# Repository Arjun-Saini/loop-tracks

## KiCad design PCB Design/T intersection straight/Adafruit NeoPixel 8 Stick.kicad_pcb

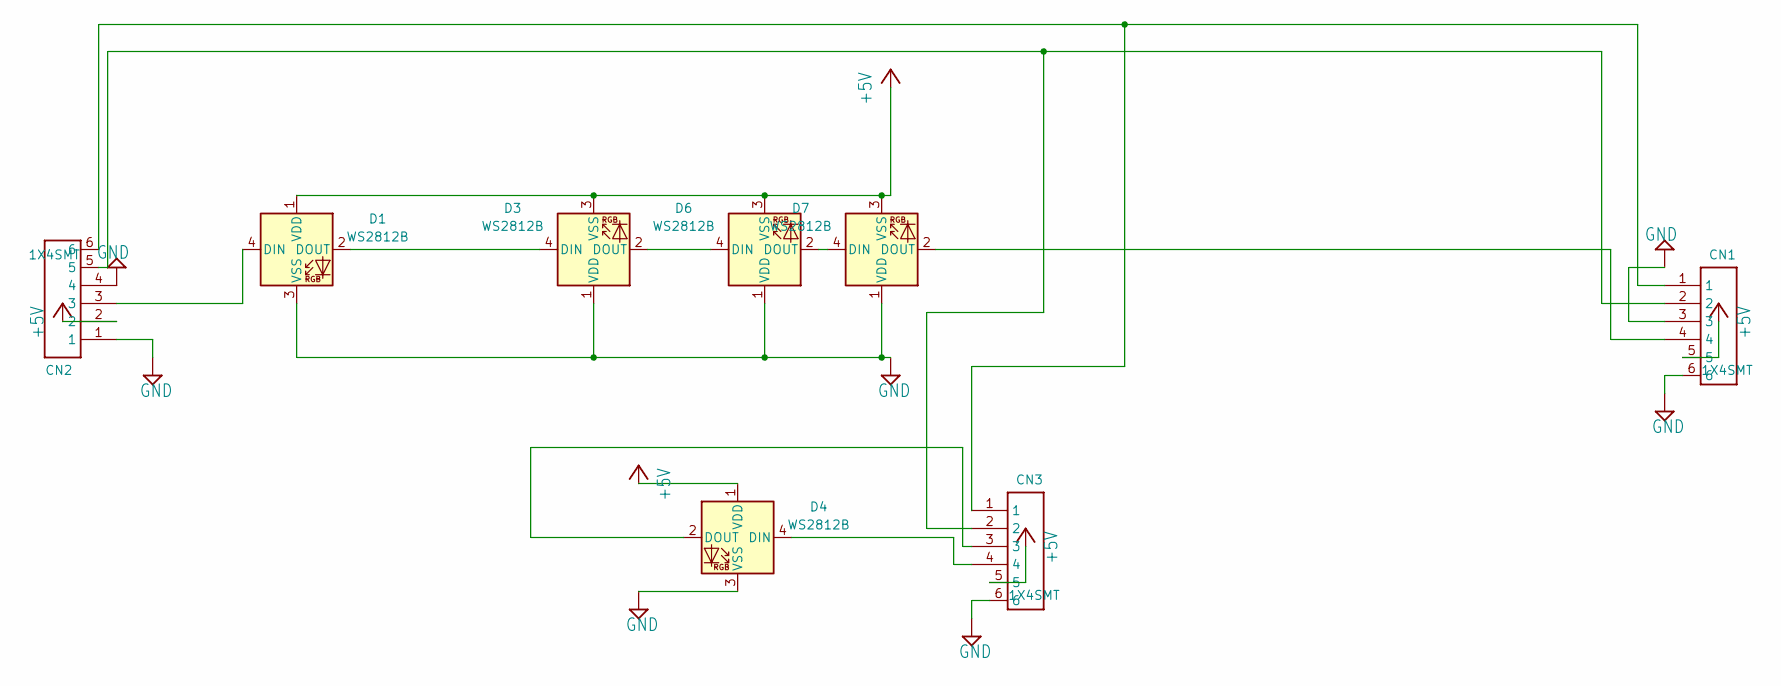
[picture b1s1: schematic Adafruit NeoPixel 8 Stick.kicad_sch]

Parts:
CN1, CN2, CN3: 1X4SMT; 1X4-SMT
D1, D3, D4, D6, D7: WS2812B; LED_WS2812B_PLCC4_5.0x5.0mm_P3.2mm

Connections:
+5V: CN1.5, CN2.2, CN3.5, D1.1 (VDD), D3.3 (VSS), D4.1 (VDD), D6.3 (VSS), D7.3 (VSS)
GND: CN1.3, CN1.6, CN2.1, CN2.4, CN3.6, D1.3 (VSS), D3.1 (VDD), D4.3 (VSS), D6.1 (VDD), D7.1 (VDD)
unnamed: CN1.1, CN2.6, CN3.1
unnamed: CN1.2, CN2.5, CN3.2
unnamed: CN1.4, D7.2 (DOUT)
unnamed: CN2.3, D1.4 (DIN)
unnamed: CN3.3, D4.2 (DOUT)
unnamed: CN3.4, D4.4 (DIN)
unnamed: D1.2 (DOUT), D3.4 (DIN)
unnamed: D3.2 (DOUT), D6.4 (DIN)
unnamed: D6.2 (DOUT), D7.4 (DIN)

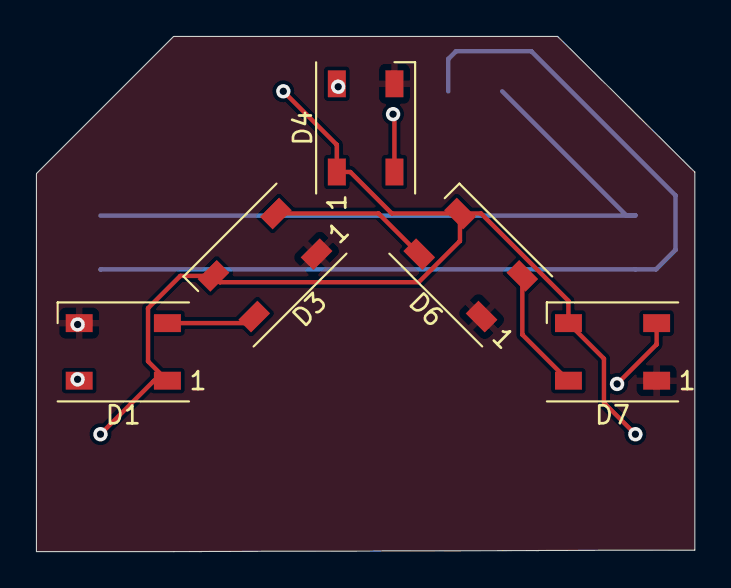
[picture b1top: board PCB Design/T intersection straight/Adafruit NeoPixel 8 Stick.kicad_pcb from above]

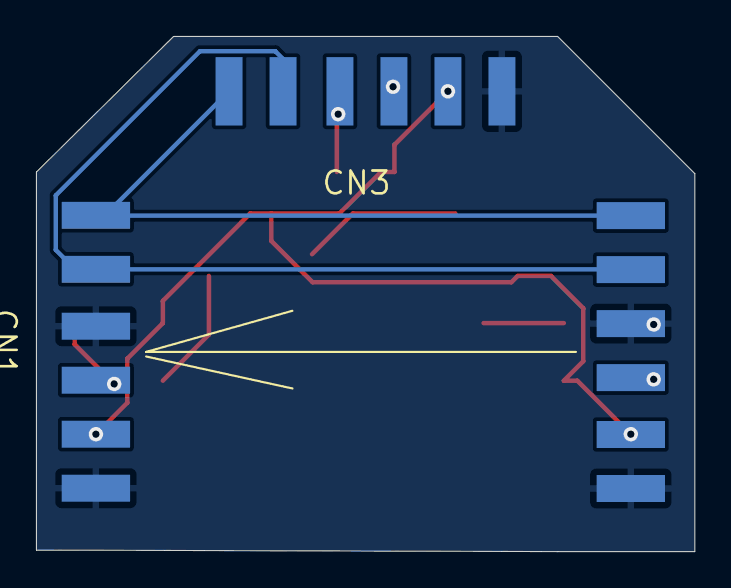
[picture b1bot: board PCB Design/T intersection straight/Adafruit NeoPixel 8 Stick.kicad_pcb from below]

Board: 2 copper layers, 36.6 x 28.6 mm, 8 parts (3 on the bottom side), 11 nets.

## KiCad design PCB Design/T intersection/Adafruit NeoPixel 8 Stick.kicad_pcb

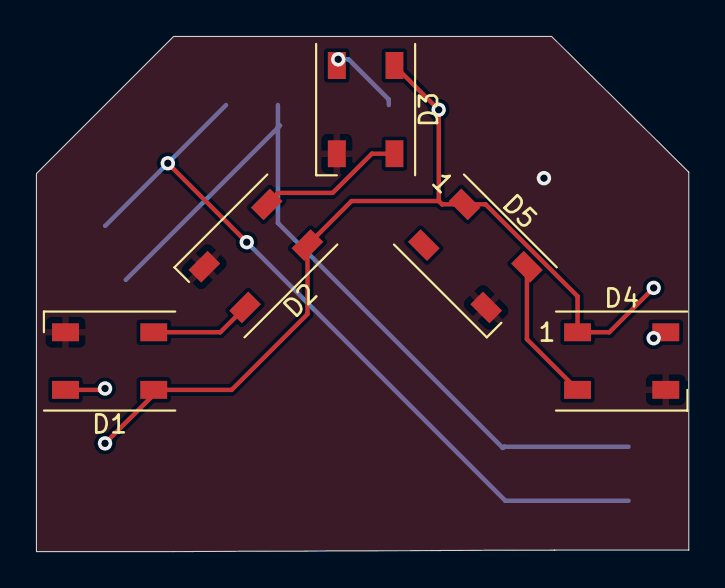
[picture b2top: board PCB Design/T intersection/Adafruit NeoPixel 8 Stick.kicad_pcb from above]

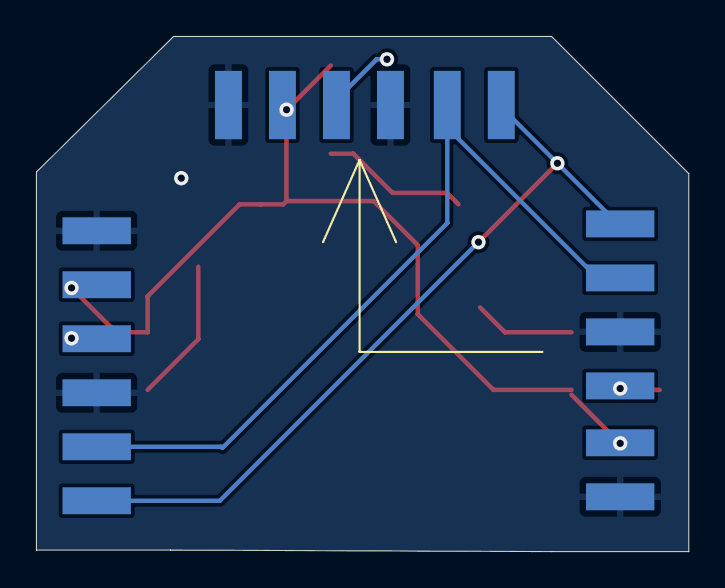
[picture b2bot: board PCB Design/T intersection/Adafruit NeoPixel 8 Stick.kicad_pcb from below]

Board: 2 copper layers, 36.2 x 28.6 mm, 8 parts (3 on the bottom side), 10 nets.

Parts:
CN1, CN2, CN3: 1X4SMT; 1X4-SMT
D1, D2, D3, D4, D5: WS2812B; LED_WS2812B_PLCC4_5.0x5.0mm_P3.2mm

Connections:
+5V: CN1.5, CN2.2, CN3.2, D1.1 (VDD), D2.1 (VDD), D3.1 (VDD), D4.1 (VDD), D5.1 (VDD)
GND: CN1.3, CN1.6, CN2.1, CN2.4, CN3.1, CN3.4, D1.3 (VSS), D2.3 (VSS), D3.3 (VSS), D4.3 (VSS), D5.3 (VSS)
unnamed: CN1.1, CN2.6, CN3.6
unnamed: CN1.2, CN2.5, CN3.5
unnamed: CN1.4, D3.2 (DOUT)
unnamed: CN2.3, D1.4 (DIN)
unnamed: CN3.3, D4.4 (DIN)
unnamed: D1.2 (DOUT), D2.4 (DIN)
unnamed: D2.2 (DOUT), D3.4 (DIN)
unnamed: D4.2 (DOUT), D5.4 (DIN)

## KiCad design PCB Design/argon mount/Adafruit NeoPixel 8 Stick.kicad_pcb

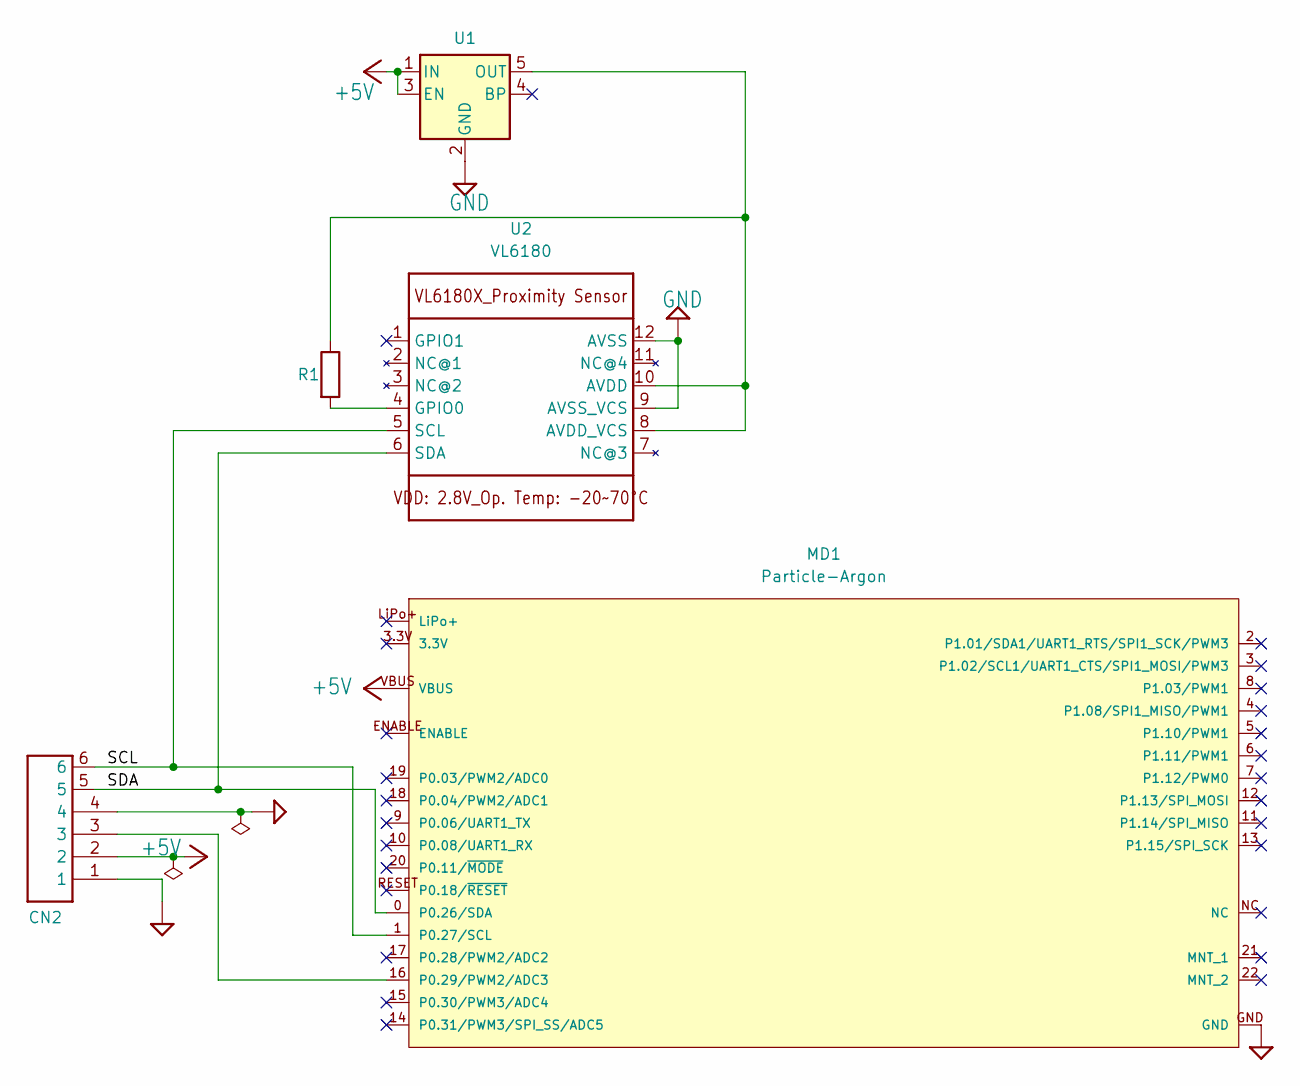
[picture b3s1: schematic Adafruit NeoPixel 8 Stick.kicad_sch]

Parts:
CN2: 1X4SMT; 1X4-SMT
MD1: Particle-Argon; Particle-Argon-0-0-MD1; manufacturer Particle; digikey description Bluetooth, WiFi 802.11b/g/n, Bluetooth 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
R1: R; R_Axial_DIN0207_L6.3mm_D2.5mm_P7.62mm_Horizontal
U1: MIC5219-2.85YM5; SOT-23-5
U2: VL6180

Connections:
+5V: CN2.2, MD1.VBUS, U1.1 (IN), U1.3 (EN)
/SCL: CN2.6, MD1.1 (P0.27/SCL), U2.5 (SCL)
/SDA: CN2.5, MD1.0 (P0.26/SDA), U2.6 (SDA)
GND: CN2.1, CN2.4, MD1.GND, U1.2 (GND), U2.9 (AVSS_VCS), U2.12 (AVSS)
unnamed: CN2.3, MD1.16 (P0.29/PWM2/ADC3)
unnamed: R1.1, U1.5 (OUT), U2.8 (AVDD_VCS), U2.10 (AVDD)
unnamed: R1.2, U2.4 (GPIO0)

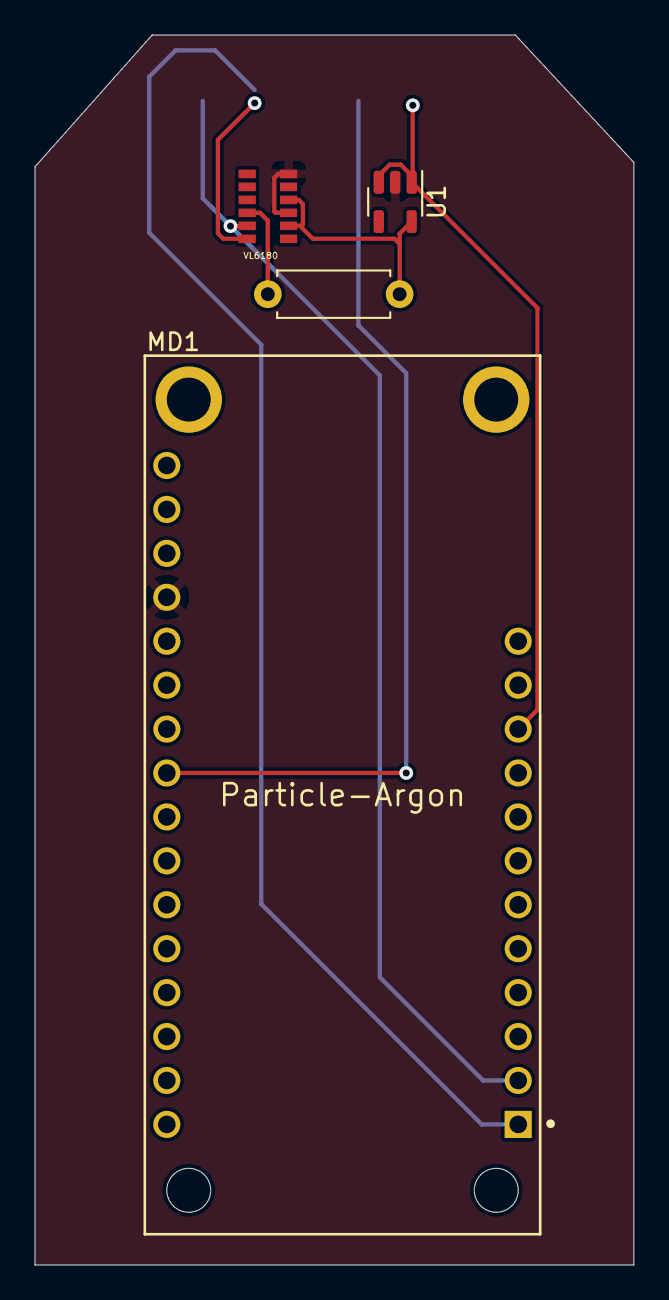
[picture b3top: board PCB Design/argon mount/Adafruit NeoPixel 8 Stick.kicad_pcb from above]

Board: 2 copper layers, 34.6 x 71.1 mm, 5 parts (1 on the bottom side), 7 nets.

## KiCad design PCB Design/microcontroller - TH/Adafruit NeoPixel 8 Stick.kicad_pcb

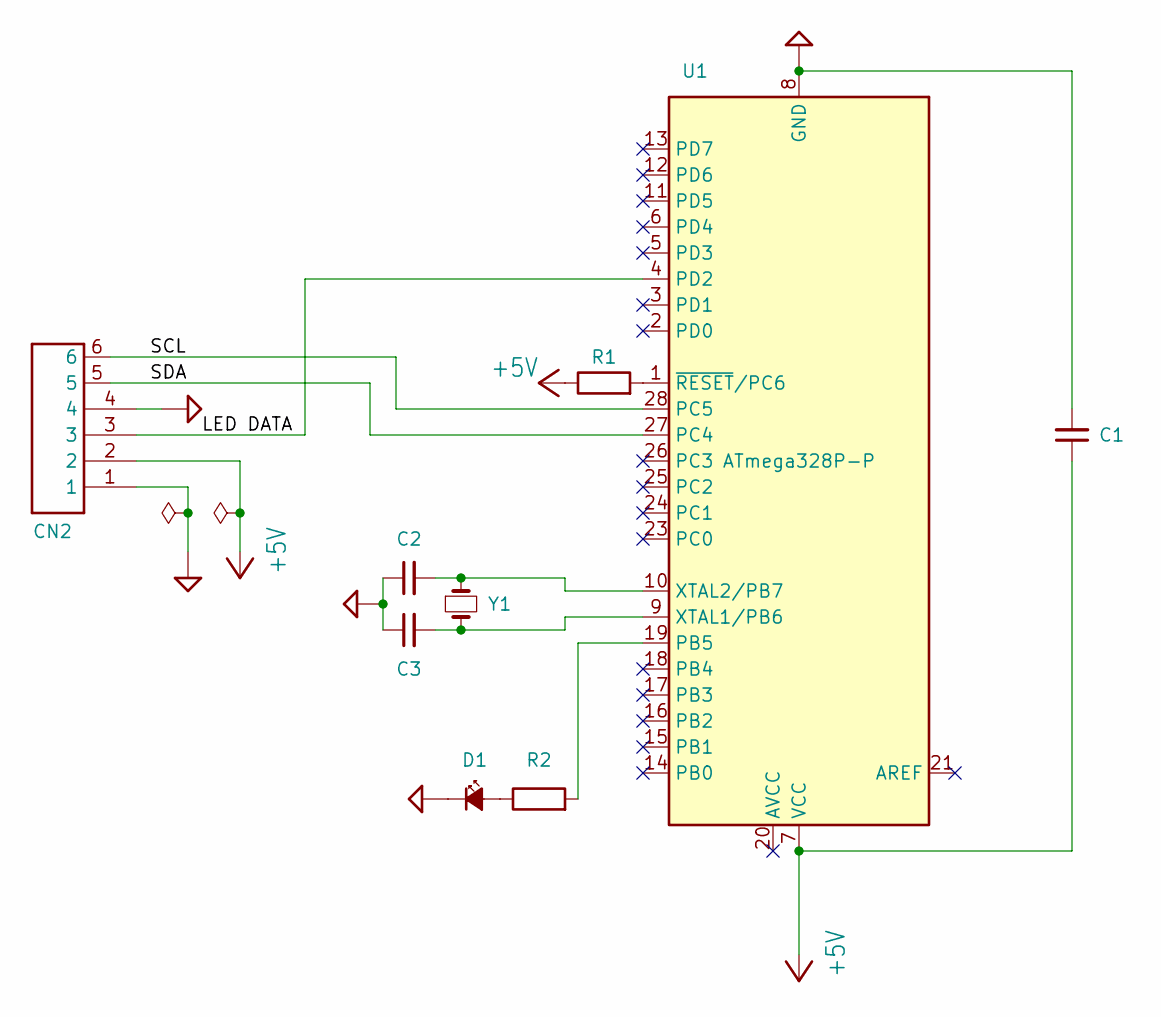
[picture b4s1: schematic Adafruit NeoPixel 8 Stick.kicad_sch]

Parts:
C1, C2, C3: C_Small; C_Disc_D4.7mm_W2.5mm_P5.00mm
CN2: 1X4SMT; 1X4-SMT
D1: LED_Small_Filled; LED_D3.0mm
R1, R2: R; R_Axial_DIN0207_L6.3mm_D2.5mm_P7.62mm_Horizontal
U1: ATmega328P-P; DIP-28_W7.62mm
Y1: Crystal_Small; Crystal_HC49-U_Vertical

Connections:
+5V: C1.1, CN2.2, R1.1, U1.7 (VCC)
/LED DATA: CN2.3, U1.4 (PD2)
/SCL: CN2.6, U1.28 (PC5)
/SDA: CN2.5, U1.27 (PC4)
GND: C1.2, C2.1, C3.1, CN2.1, CN2.4, D1.1 (K), U1.8 (GND), U1.22 (GND)
unnamed: C2.2, U1.10 (XTAL2/PB7), Y1.1
unnamed: C3.2, U1.9 (XTAL1/PB6), Y1.2
unnamed: D1.2 (A), R2.1
unnamed: R1.2, U1.1 (~RESET/PC6)
unnamed: R2.2, U1.19 (PB5)

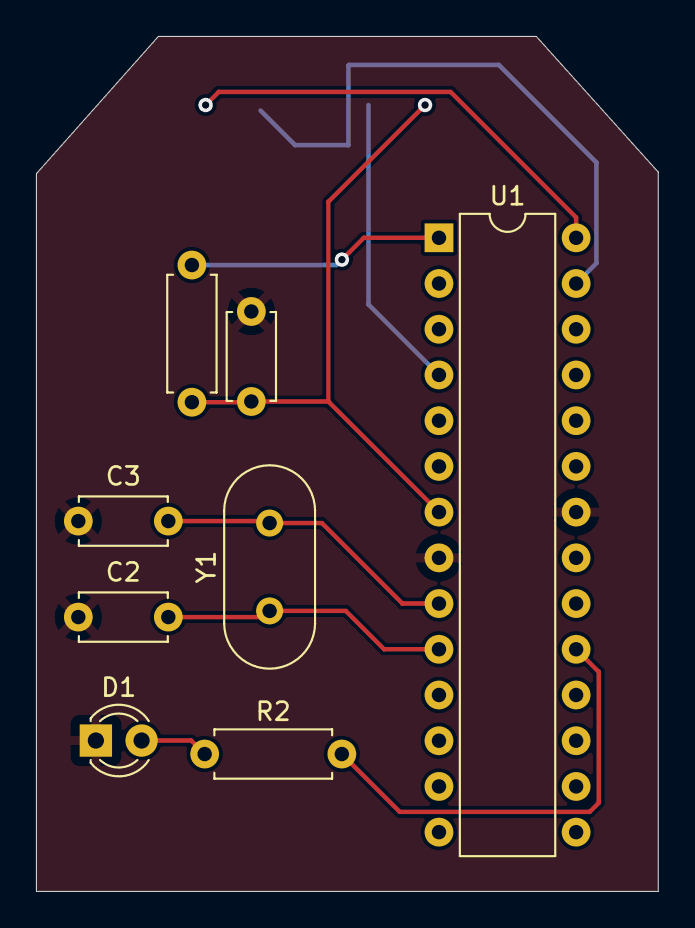
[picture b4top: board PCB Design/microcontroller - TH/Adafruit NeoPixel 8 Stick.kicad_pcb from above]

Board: 2 copper layers, 34.5 x 47.5 mm, 9 parts (1 on the bottom side), 10 nets.

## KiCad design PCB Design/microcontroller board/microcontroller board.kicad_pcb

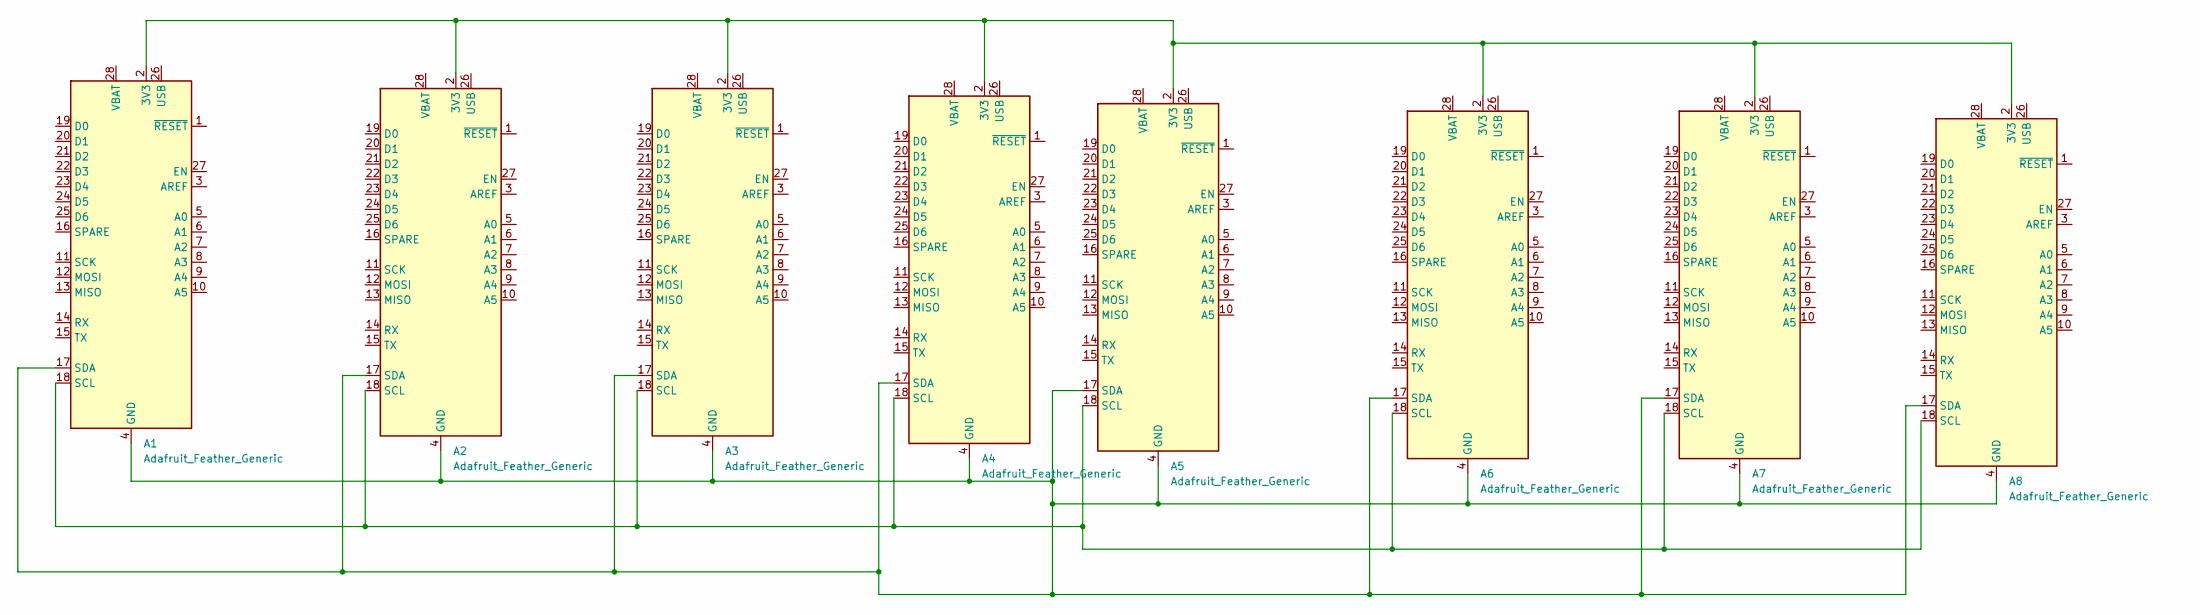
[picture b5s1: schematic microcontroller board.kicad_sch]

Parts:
A1, A2, A3, A4, A5, A6, A7, A8: Adafruit_Feather_Generic; Adafruit_Feather

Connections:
unnamed: A1.2 (3V3), A2.2 (3V3), A3.2 (3V3), A4.2 (3V3), A5.2 (3V3), A6.2 (3V3), A7.2 (3V3), A8.2 (3V3)
unnamed: A1.4 (GND), A1.17 (SDA), A2.4 (GND), A2.17 (SDA), A3.4 (GND), A3.17 (SDA), A4.4 (GND), A4.17 (SDA), A5.4 (GND), A5.17 (SDA), A6.4 (GND), A6.17 (SDA), A7.4 (GND), A7.17 (SDA), A8.4 (GND), A8.17 (SDA)
unnamed: A1.18 (SCL), A2.18 (SCL), A3.18 (SCL), A4.18 (SCL), A5.18 (SCL), A6.18 (SCL), A7.18 (SCL), A8.18 (SCL)

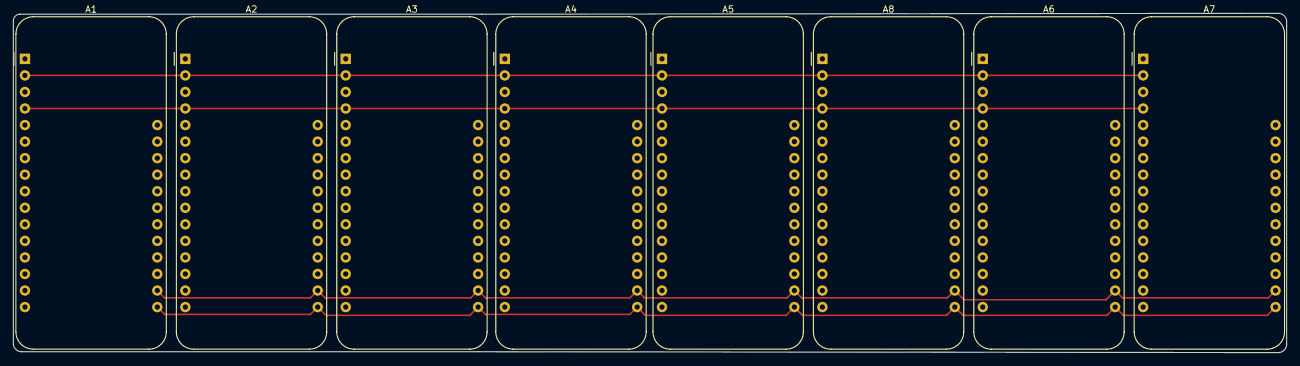
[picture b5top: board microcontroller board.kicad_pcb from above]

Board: 2 copper layers, 195.5 x 52.1 mm, 8 parts (0 on the bottom side), 3 nets.

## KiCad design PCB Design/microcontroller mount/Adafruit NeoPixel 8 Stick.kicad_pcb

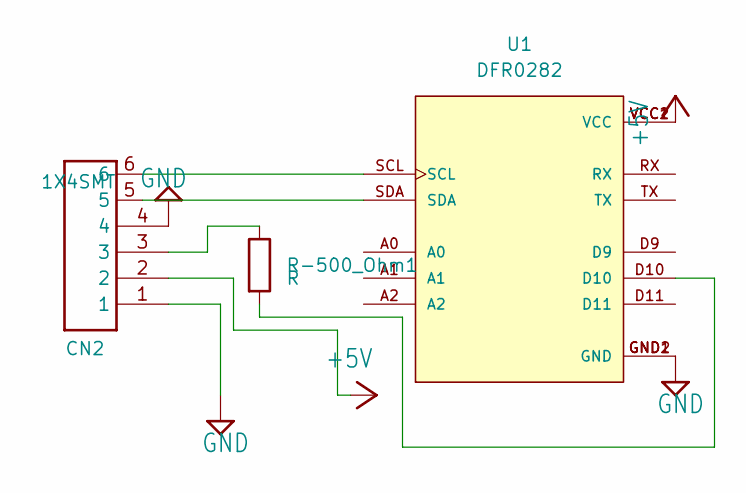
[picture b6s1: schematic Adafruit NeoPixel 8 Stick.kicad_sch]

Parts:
CN2: 1X4SMT; 1X4-SMT
R-500_Ohm1: R; R_Axial_DIN0207_L6.3mm_D2.5mm_P7.62mm_Horizontal
U1: DFR0282

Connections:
+5V: CN2.2, U1.VCC1 (VCC), U1.VCC2 (VCC)
GND: CN2.1, CN2.4, U1.GND1 (GND), U1.GND2 (GND)
unnamed: CN2.3, R-500_Ohm1.1
unnamed: CN2.5, U1.SDA
unnamed: CN2.6, U1.SCL
unnamed: R-500_Ohm1.2, U1.D10

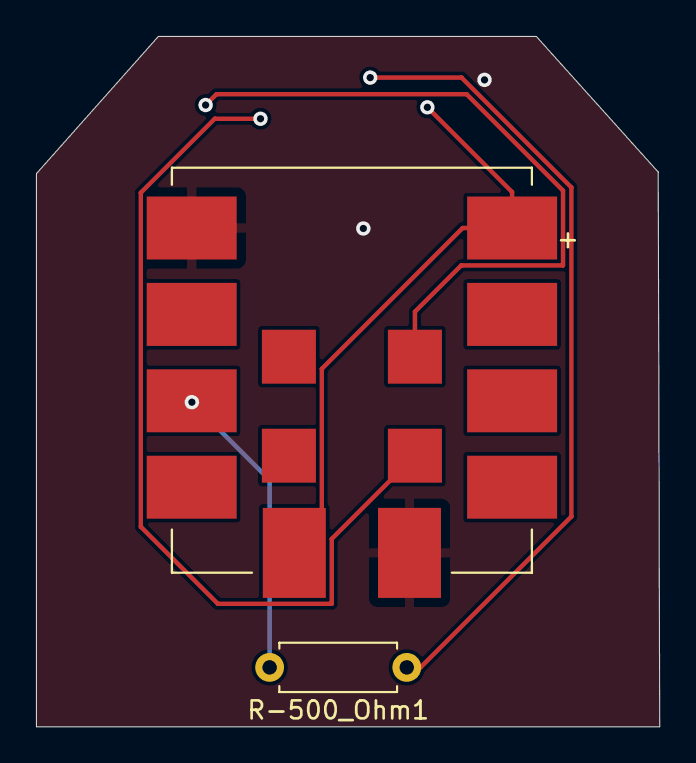
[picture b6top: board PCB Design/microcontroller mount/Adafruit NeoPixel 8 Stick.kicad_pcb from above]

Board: 2 copper layers, 34.6 x 38.4 mm, 3 parts (1 on the bottom side), 6 nets.

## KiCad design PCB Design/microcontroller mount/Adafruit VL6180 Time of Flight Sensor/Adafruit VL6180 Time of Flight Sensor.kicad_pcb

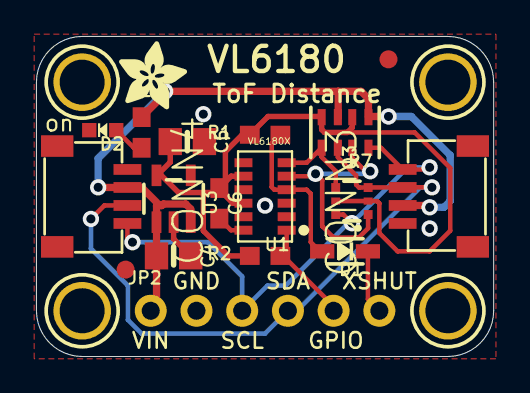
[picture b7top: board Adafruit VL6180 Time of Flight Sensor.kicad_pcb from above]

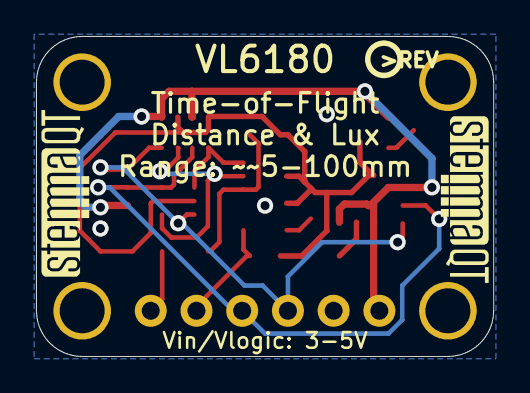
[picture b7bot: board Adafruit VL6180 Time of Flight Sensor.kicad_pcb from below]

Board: 2 copper layers, 25.4 x 17.8 mm, 25 parts (3 on the bottom side), 11 nets.

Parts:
C4, C5: 10uF; 0805-NO
C6: 0.1uF; 0603-NO
CONN3, CONN4: STEMMA_I2C_QT; JST_SH4
D1: 1N4148; SOD-323
D2: GREEN; CHIPLED_0603_NOOUTLINE
FID1, FID4: FIDUCIAL_1MM
JP2: 1X06_ROUND_70
Q3: BSS138; SOT363
R1, R2, R3: 10K; 0603-NO
R7: 10K; RESPACK_4X0603
U1: VL6180X; VL6180
U3: LP5907-2.8V; SOT23-5
U$30, U$31, U$33, U$34: MOUNTINGHOLE2.5; MOUNTINGHOLE_2.5_PLATED
U$36: ADAFRUIT_3.5MM
U$37: PCBFEAT-REV-040
U$38, U$39: STEMMAQT

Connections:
2.8V: C5.1, C6.1, Q3.2, Q3.5, R1.2, R2.2, R7.2, R7.4, U1.8, U1.10, U3.5
GND: C4.2, C5.2, C6.2, CONN3.1, CONN4.1, D2.C, JP2.2, U1.9, U1.12, U3.2
GPIO: JP2.5, R2.1, U1.1
unnamed: D2.A, R3.1
SCL: CONN3.4, CONN4.4, JP2.3, Q3.6, R7.8
SCL_3V: Q3.1, R7.7, U1.5
SDA: CONN3.3, CONN4.3, JP2.4, Q3.3, R7.6
SDA_3V: Q3.4, R7.5, U1.6
VCC: C4.1, CONN3.2, CONN4.2, JP2.1, R3.2, R7.1, R7.3, U3.1, U3.3
XSHUT: D1.C, JP2.6
XSHUT_2.8V: D1.A, R1.1, U1.4

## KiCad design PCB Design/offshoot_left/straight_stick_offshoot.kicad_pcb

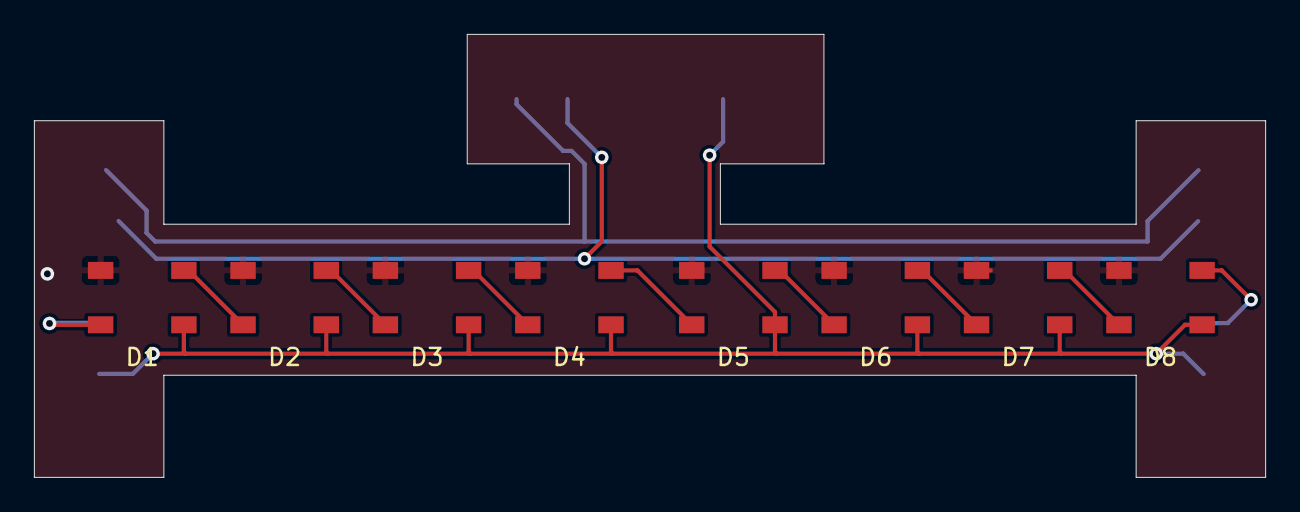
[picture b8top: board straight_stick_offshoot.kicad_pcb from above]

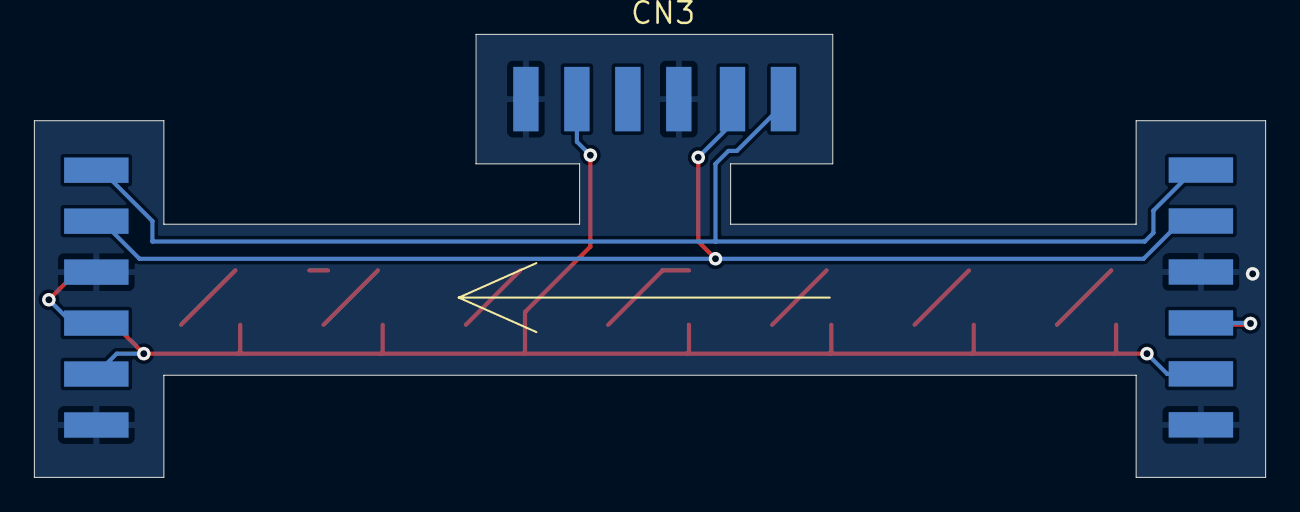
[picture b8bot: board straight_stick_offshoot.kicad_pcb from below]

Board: 2 copper layers, 72.5 x 26.1 mm, 11 parts (3 on the bottom side), 13 nets.

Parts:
CN1, CN2, CN3: 1X4SMT; 1X4-SMT
D1, D2, D3, D4, D5, D6, D7, D8: WS2812B; LED_WS2812B_PLCC4_5.0x5.0mm_P3.2mm

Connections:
+5V: CN1.5, CN2.2, CN3.5, D1.1 (VDD), D2.1 (VDD), D3.1 (VDD), D4.1 (VDD), D5.1 (VDD), D6.1 (VDD), D7.1 (VDD), D8.1 (VDD)
GND: CN1.3, CN1.6, CN2.1, CN2.4, CN3.3, CN3.6, D1.3 (VSS), D2.3 (VSS), D3.3 (VSS), D4.3 (VSS), D5.3 (VSS), D6.3 (VSS), D7.3 (VSS), D8.3 (VSS)
unnamed: CN1.1, CN2.6, CN3.1
unnamed: CN1.2, CN2.5, CN3.2
unnamed: CN1.4, D8.2 (DOUT)
unnamed: CN2.3, D1.4 (DIN)
unnamed: D1.2 (DOUT), D2.4 (DIN)
unnamed: D2.2 (DOUT), D3.4 (DIN)
unnamed: D3.2 (DOUT), D4.4 (DIN)
unnamed: D4.2 (DOUT), D5.4 (DIN)
unnamed: D5.2 (DOUT), D6.4 (DIN)
unnamed: D6.2 (DOUT), D7.4 (DIN)
unnamed: D7.2 (DOUT), D8.4 (DIN)
